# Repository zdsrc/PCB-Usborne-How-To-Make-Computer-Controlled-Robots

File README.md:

# Usborne Robot

This is a PCB for the circuit from the Usborne book "How To Make
Computer-Controlled Robots".

**Status: untested, use at your own risk.**

As Usborne Publishing themselves releasing their book titles 
“Practice Your BASIC”, “Better BASIC”, “Computer Controlled Robots”, 
“Experiments With Your Computer”, and “Keyboards & Computer Music”, 
as PDFs, book  “Computer Controlled Robots” is added to folder.

Related news:
https://retro-hardware.com/2017/06/21/1980-retro-computer-books-from-usborne-free-to-download/
https://hackaday.com/2017/03/20/usborne-release-more-1980s-computer-books/

Book(s) can be downloaded from:
https://usborne.com/row/books/computer-and-coding-books

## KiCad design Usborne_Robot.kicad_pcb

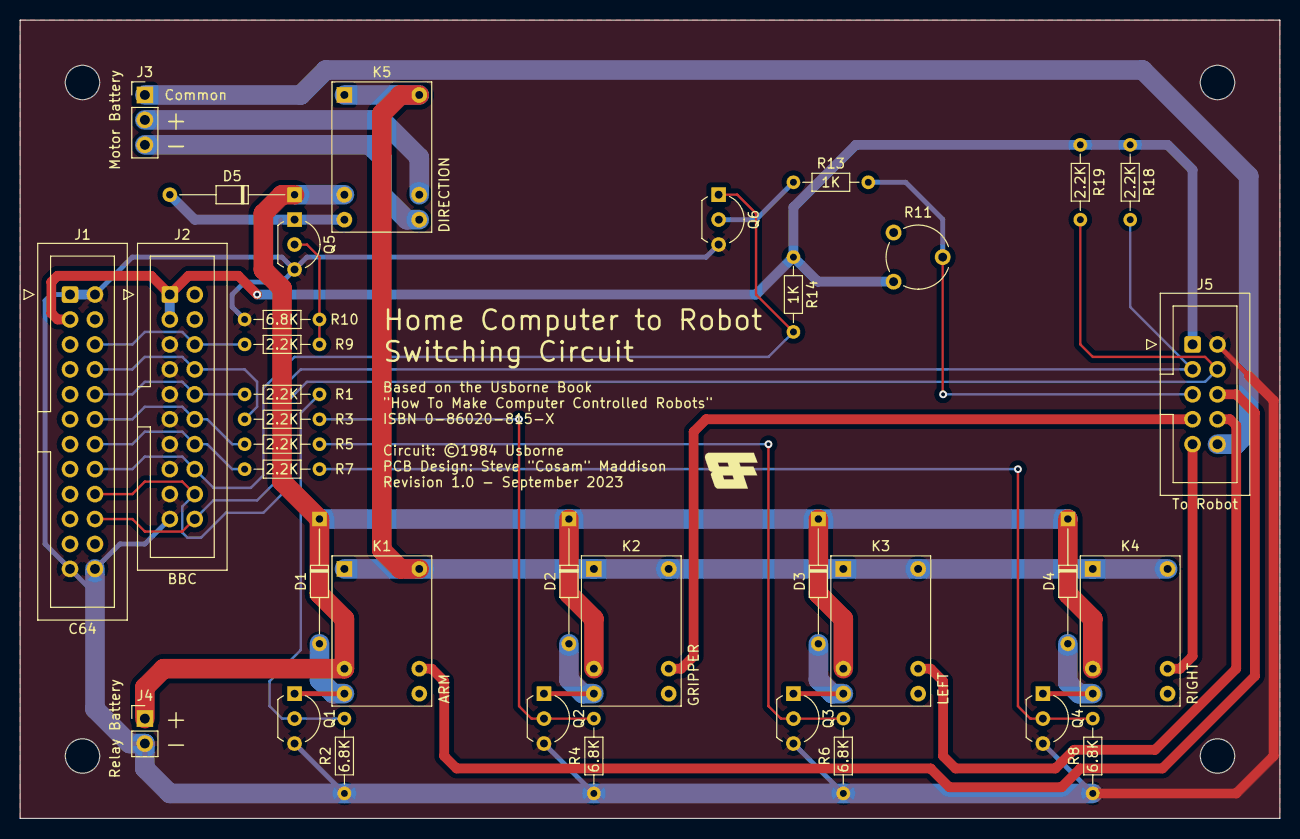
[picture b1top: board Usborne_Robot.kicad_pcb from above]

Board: 2 copper layers, 128.3 x 81.3 mm, 36 parts (0 on the bottom side), 31 nets.

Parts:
D1, D2, D3, D4, D5: 1N4001; D_DO-34_SOD68_P12.70mm_Horizontal
J1: C64; C64-IO_Port_Header
J2: BBC; IDC-Header_2x10_P2.54mm_Vertical
J3: Motor Battery; PinHeader_1x03_P2.54mm_Vertical
J4: Relay Battery; PinHeader_1x02_P2.54mm_Vertical
J5: To Robot; IDC-Header_2x05_P2.54mm_Vertical
K1: ARM; Relay_DIP-12
K2: GRIPPER; Relay_DIP-12
K3: LEFT; Relay_DIP-12
K4: RIGHT; Relay_DIP-12
K5: DIRECTION; Relay_DIP-12
Q1, Q2, Q3, Q4, Q5, Q6: BC108; TO-92L_Inline_Wide
R1, R3, R5, R7, R9, R18, R19: 2.2K; R_Axial_DIN0204_L3.6mm_D1.6mm_P7.62mm_Horizontal
R2, R4, R6, R8, R10: 6.8K; R_Axial_DIN0204_L3.6mm_D1.6mm_P7.62mm_Horizontal
R11: 100K; Potentiometer_Piher_PT-6-V_Vertical
R13, R14: 1K; R_Axial_DIN0204_L3.6mm_D1.6mm_P7.62mm_Horizontal

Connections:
+5V: J1.2, J2.1, J2.3, J5.1, R11.1, R14.2, R18.1, R19.1
+12V: D1.1 (K), D2.1 (K), D3.1 (K), D4.1 (K), D5.1 (K), J4.1, K1.5, K2.5, K3.5, K4.5, K5.5
GND: J1.1, J1.12, J1.A (Pin_24), J1.N (Pin_13), J2.5, J2.7, J2.9, J2.11, J2.13, J2.15, J2.17, J2.19, J4.2, J5.2, Q1.3 (E), Q2.3 (E), Q3.3 (E), Q4.3 (E), Q5.3 (E), Q6.3 (E), R2.1, R4.1, R6.1, R8.1, R10.1
MOTOR: K1.1, K1.12, K2.1, K2.12, K3.1, K3.12, K4.1, K4.12, K5.1, K5.12
MOTOR_ARM: J5.6, K1.8
MOTOR_COMMON: J3.1, J5.10
MOTOR_GRIPPER: J5.7, K2.8
MOTOR_LEFT: J5.8, K3.8
MOTOR_RIGHT: J5.9, K4.8
unnamed: D1.2 (A), K1.6, Q1.1 (C)
unnamed: D2.2 (A), K2.6, Q2.1 (C)
unnamed: D3.2 (A), K3.6, Q3.1 (C)
unnamed: D4.2 (A), K4.6, Q4.1 (C)
unnamed: D5.2 (A), K5.6, Q5.1 (C)
unnamed: J3.2, K5.8
unnamed: J3.3, K5.7
unnamed: Q1.2 (B), R1.2, R2.2
unnamed: Q2.2 (B), R3.2, R4.2
unnamed: Q3.2 (B), R5.2, R6.2
unnamed: Q4.2 (B), R7.2, R8.2
unnamed: Q5.2 (B), R9.2, R10.2
unnamed: Q6.2 (B), R13.1
PB0: J1.C (Pin_22), J2.6, R9.1
PB1: J1.D (Pin_21), J2.8, R3.1
PB2: J1.E (Pin_20), J2.10, R1.1
PB3: J1.F (Pin_19), J2.12, R5.1
PB4: J1.H (Pin_18), J2.14, R7.1
PB5: J1.J (Pin_17), J2.16, Q6.1 (C), R14.1
PB6: J1.K (Pin_16), J2.18, J5.4, R19.2
PB7: J1.L (Pin_15), J2.20, J5.3, R18.2
SENSOR_LIGHT: J5.5, R11.2, R13.2

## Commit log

2023-09-26 Initial revision
2023-09-27 Thicker traces for motor signals, wide footprints for transistors.
2025-03-21 Add README
2026-03-11 Usborne Publishing released Computer Controlled Robots as free pdf, added book to repo

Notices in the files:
Usborne_Robot.kicad_pcb:
Circuit: ©1984 Usborne
